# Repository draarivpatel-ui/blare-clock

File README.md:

# BlareClock - My XIAO ESP32-C3 Desk Alarm Clock with 2.25" ST7789 TFT & DS3231 RTC

**Try the Live Interactive Clock & Hardware Inspector:** [https://aariv.me/blare-clock/](https://aariv.me/blare-clock/)

I designed and built **BlareClock** for the Hack Club Stardance **BLARE** alarm clock mission. It is a dedicated hardware desk alarm clock powered by a **Seeed Studio XIAO ESP32-C3**, a wide-aspect **2.25" ST7789 SPI TFT bar display (284x76 IPS)**, a **DS3231 temperature-compensated I2C real-time clock (TCXO)** with CR2032 coin-cell backup, a **12mm 85dB passive piezo buzzer**, and **four front-facing Omron tactile push buttons**.

In addition to the complete KiCad 8 schematic, 2-layer carrier PCB (`92.0mm x 54.0mm`), JLCPCB Gerber archive, 15-degree angled OpenSCAD desk enclosure STLs, and ESP32-C3 Arduino firmware, I also built an interactive browser simulator at [https://aariv.me/blare-clock/](https://aariv.me/blare-clock/) where you can test the live 284x76 IPS clock UI, set alarms, trigger the 85dB piezo wake-up melody via Web Audio, inspect the 2-layer PCB traces, and orbit the 3D exploded CAD housing.

## Why I Built This

For years I used my phone as my morning alarm clock, which meant keeping notifications and a glowing screen within arm's reach of my bed every night. On the flip side, cheap digital bedside clocks drift by several minutes a month and lose their time entirely whenever a wall outlet flickers.

I wanted to build a dedicated, zero-distraction hardware desk clock that solves both problems:
1. **Sub-second accuracy that survives power outages**: When `BlareClock` boots, the **XIAO ESP32-C3** connects briefly to Wi-Fi, pulls UTC time from `pool.ntp.org`, and writes that exact timestamp into a battery-backed **DS3231 TCXO real-time clock**. Even if Wi-Fi is down or the USB-C cable is unplugged, the CR2032-backed DS3231 keeps time within `±2 ppm` (`~1 minute per year`) and exposes an onboard die temperature sensor (`±0.25°C` resolution) for the status bar.
2. **Wide-aspect high-contrast digits (`284x76 IPS`)**: Instead of a cramped 128x64 OLED or blinding 7-segment LEDs, I chose a wide 2.25" ST7789 bar TFT so the `HH:MM:SS` readout, armed alarm time, snooze badge, and room temperature fit side by side in crisp typography.
3. **Physical tactile controls & an unmistakable alarm**: Four front-mounted tactile switches (`SNOOZE`, `ALARM SET`, `PLUS +`, `MINUS -`) and a 4-note escalating passive piezo cascade (`C6 -> E6 -> G6 -> C7`) make sure I can operate it by feel at 6:30 AM.

## Features & How It Works Under the Hood

### 1. Five-State Alarm & Snooze State Machine (`firmware/blare_clock.ino`)
I structured the ESP32-C3 firmware around a deterministic 5-state controller:
- **`STATE_CLOCK_NORMAL`**: Renders the live `HH:MM:SS` readout at 10Hz, polls the DS3231 temperature register every 30 seconds, and checks for exact `hour == alarmHour && minute == alarmMin && second == 0` matches when armed. Pressing `SNOOZE` in normal mode toggles `alarmArmed`.
- **`STATE_EDIT_ALARM_HOUR` & `STATE_EDIT_ALARM_MIN`**: Pressing `ALARM SET` highlights the alarm hour field in amber so `PLUS +` and `MINUS -` increment/decrement with wrap-around (`0..23`); pressing `ALARM SET` again shifts to minutes (`0..59`), and a third press commits the new alarm to `Preferences` NVRAM and arms the clock.
- **`STATE_ALARM_RINGING`**: Flashes the wide TFT border in high-contrast crimson and drives the passive piezo buzzer (`GPIO21` LEDC PWM) with an escalating 4-tone square-wave arpeggio (`1046Hz`, `1318Hz`, `1568Hz`, `2093Hz`). Pressing `SNOOZE` enters a 9-minute snooze countdown; pressing `ALARM SET` dismisses the alarm for the day.
- **`STATE_SNOOZING`**: Displays a live `SNOOZE 08:59` countdown badge on the ST7789 screen and automatically re-triggers `STATE_ALARM_RINGING` when the 540-second timer expires.

### 2. 2-Layer 92mm x 54mm Carrier PCB & 15° Angled Enclosure
- **Carrier PCB (`pcb/blare_clock.kicad_pcb`)**: Places the 2.25" ST7789 display module top-center (`Y = 6..34mm`) directly above the four 6mm Omron tactile buttons (`SW1..SW4` at `Y = 45mm`, spaced `18mm` apart) so the entire front face acts as the user interface while the XIAO ESP32-C3, DS3231 RTC module, and 12mm piezo transducer mount cleanly on the rear/inner carrier zone.
- **Angled Desk Housing (`cad/blare_enclosure.scad`)**: Designed with a `15-degree` backward tilt so the display faces your eyes naturally on a desk or nightstand. Includes acoustic louver slots on the rear housing over `BZ1`, a recessed front bezel for the 2.25" glass panel, and a captive 4-button actuator bar (`~72g` total PLA).

## What Was Tricky to Build

1. **Keeping the XIAO ESP32-C3 Boot Strap Pins Safe**:
   On the ESP32-C3, `GPIO8`, `GPIO9`, and `GPIO2` have boot-strapping behaviors if pulled to the wrong logic level during power-on reset. I wired `GPIO8` (`D8`) as `TFT_SCK` and `GPIO9` (`D9`) as `TFT_CS` with external/internal pull-ups so the chip always boots cleanly into normal SPI flash execution mode, even if you hold down `SNOOZE` (`D0 / GPIO2` with internal pull-up) while plugging in USB-C.
2. **Eliminating Display Flicker on the 284x76 ST7789 Panel**:
   Redrawing the full `284x76` SPI framebuffer on every loop iteration caused visible tearing on the seconds counter. In `firmware/blare_clock.ino`, I tracked `lastRenderedSecond` and `lastUiState` so SPI region updates only fire when a digit or state actually changes, keeping the display rock-solid while leaving plenty of CPU headroom for the non-blocking piezo sequencer.

## XIAO ESP32-C3 Pinout & Carrier Wiring

| Seeed XIAO ESP32-C3 Pin | Net Name | Connected Hardware |
| --- | --- | --- |
| `D0 / GPIO2` | `BTN_SNOOZE` | `SW1` Tactile Button (Snooze +9m / Toggle Arm) |
| `D1 / GPIO3` | `BTN_ALARM` | `SW2` Tactile Button (Cycle Set Hour / Set Minute) |
| `D2 / GPIO4` | `BTN_PLUS` | `SW3` Tactile Button (Increment Hour / Minute) |
| `D3 / GPIO5` | `BTN_MINUS` | `SW4` Tactile Button (Decrement Hour / Minute) |
| `D4 / GPIO6 (SDA)` | `I2C_SDA` | `U2` DS3231 RTC Module I2C Data (`0x68`) |
| `D5 / GPIO7 (SCL)` | `I2C_SCL` | `U2` DS3231 RTC Module I2C Clock |
| `D6 / GPIO21` | `BUZZER_PWM` | `BZ1` 12mm 85dB Passive Piezo Transducer |
| `D7 / GPIO20` | `TFT_DC` | `J1` 2.25" ST7789 SPI TFT Data/Command |
| `D8 / GPIO8 (SCK)` | `TFT_SCK` | `J1` 2.25" ST7789 SPI TFT Serial Clock |
| `D9 / GPIO9` | `TFT_CS` | `J1` 2.25" ST7789 SPI TFT Chip Select |
| `D10 / GPIO10 (MOSI)` | `TFT_MOSI` | `J1` 2.25" ST7789 SPI TFT Serial Data In |
| `3V3 / 5V / GND` | Power | Common `3V3` logic/backlight rail and stitched `GND` pour |

## Bill of Materials

| Ref | Qty | Component | Footprint / Package |
| --- | --- | --- | --- |
| `U1` | 1 | Seeed Studio XIAO ESP32-C3 | 14-Pin THT/SMD Module |
| `J1` | 1 | 2.25" ST7789 Wide SPI TFT LCD (284x76 IPS) | 8-Pin 2.54mm Header |
| `U2` | 1 | DS3231 Precision I2C RTC Module + CR2032 | 4-Pin 2.54mm Header |
| `BZ1` | 1 | 12mm 85dB Passive Piezo Buzzer (`PS1240P02BT`) | `MagneticBuzzer_12x9.5mm_P6.5mm` |
| `SW1-SW4` | 4 | 6x6x7mm Omron Tactile Push Buttons (`B3F-1050`) | `SW_PUSH_6mm` |
| `H1-H4` | 4 | M2.5x8mm Screws + M2.5 Brass Heat-Set Inserts | 2.5mm Mounting Holes |

## Repository Structure & How to Explore It

- **Interactive Browser Simulator**: Open [https://aariv.me/blare-clock/](https://aariv.me/blare-clock/) (or open `index.html` locally) to use the live 2.25" ST7789 clock, press `ALARM SET`, `PLUS +`, `MINUS -`, `SNOOZE`, or `TRIGGER 85dB PIEZO ALARM`, inspect the 2-layer PCB copper and silkscreen layers, and orbit the 3D CAD enclosure.
- **KiCad 8 Project & Gerbers**: Open `pcb/blare_clock.kicad_pro` in KiCad 8 to inspect `pcb/blare_clock.kicad_sch` and `pcb/blare_clock.kicad_pcb`. JLCPCB-ready Gerbers are archived at `pcb/gerbers/blare-clock-gerbers.zip`.
- **3D Enclosure CAD**: Open `cad/blare_enclosure.scad` in OpenSCAD or slice `cad/front_bezel.stl`, `cad/rear_housing.stl`, and `cad/button_bar.stl`.
- **ESP32-C3 Firmware**: Open `firmware/blare_clock.ino` in Arduino IDE / PlatformIO with `RTClib` and `Adafruit_ST7789` installed.

## License

MIT.

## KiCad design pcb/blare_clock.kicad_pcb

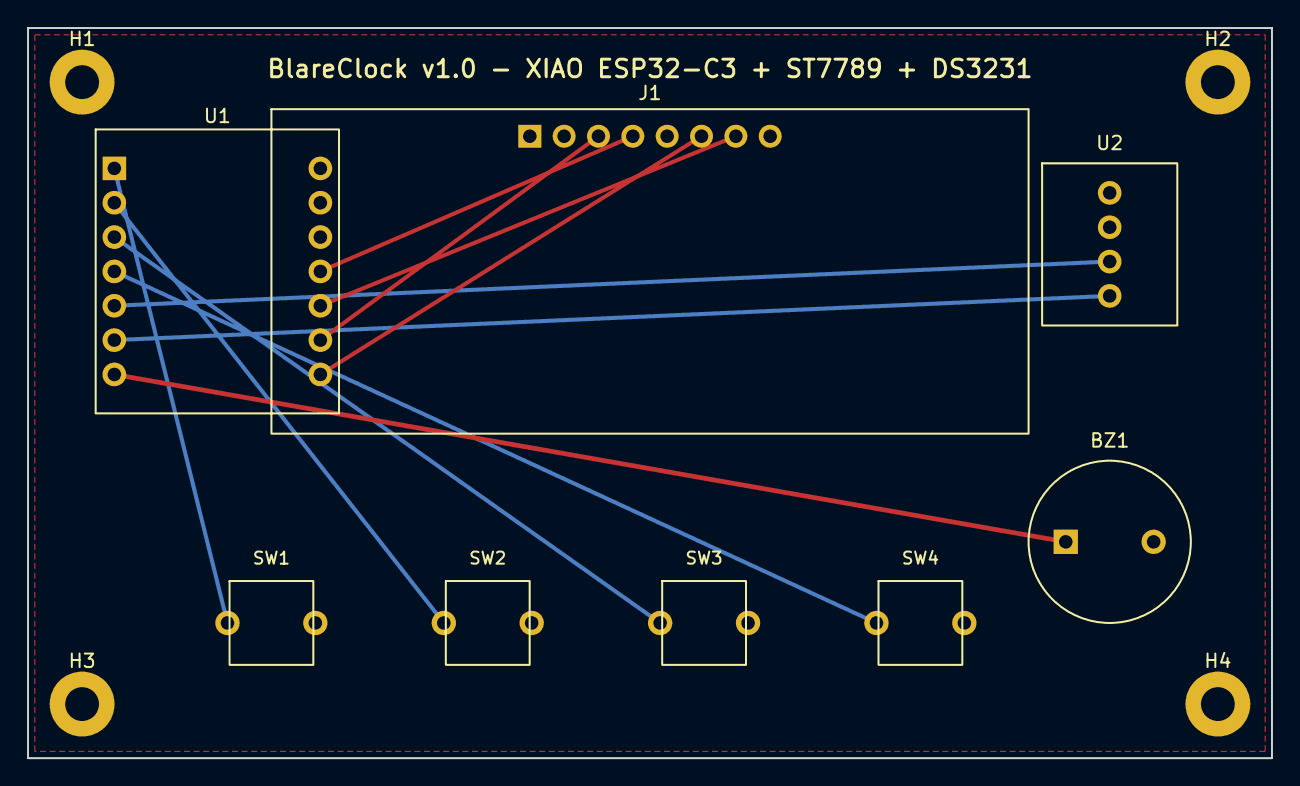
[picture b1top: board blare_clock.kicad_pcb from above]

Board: 2 copper layers, 92.0 x 54.0 mm, 12 parts (0 on the bottom side), 13 nets.

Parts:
BZ1: PIEZO_85dB; MagneticBuzzer_12x9.5mm_P6.5mm
H1, H2, H3, H4: M2.5; MountingHole_2.5mm_Pad
J1: ST7789_2.25_TFT; ST7789_2.25_284x76
SW1: SNOOZE; SW_PUSH_6mm
SW2: ALARM; SW_PUSH_6mm
SW3: PLUS; SW_PUSH_6mm
SW4: MINUS; SW_PUSH_6mm
U1: XIAO_ESP32C3; Seeed_XIAO_ESP32C3_THT
U2: DS3231_RTC; DS3231_Module_4Pin

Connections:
+3V3: J1.2, J1.5, J1.8, U1.12, U2.2
BTN_ALARM: SW2.1, U1.2
BTN_MINUS: SW4.1, U1.4
BTN_PLUS: SW3.1, U1.3
BTN_SNOOZE: SW1.1, U1.1
BUZZER_PWM: BZ1.1, U1.7
GND: BZ1.2, H1.1, H2.1, H3.1, H4.1, J1.1, SW1.2, SW2.2, SW3.2, SW4.2, U1.13, U2.1
I2C_SCL: U1.6, U2.4
I2C_SDA: U1.5, U2.3
TFT_CS: J1.7, U1.10
TFT_DC: J1.6, U1.8
TFT_MOSI: J1.4, U1.11
TFT_SCK: J1.3, U1.9

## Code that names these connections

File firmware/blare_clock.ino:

// BlareClock v1.0 - Smart Desk Alarm Clock Firmware
// Target MCU: Seeed Studio XIAO ESP32-C3 (RISC-V 160MHz + Wi-Fi NTP + Hardware RTC)
// Pinout matches pcb/blare_clock.kicad_pcb:
//   SW1 (BTN_SNOOZE): D0 (GPIO2)
//   SW2 (BTN_ALARM):  D1 (GPIO3)
//   SW3 (BTN_PLUS):   D2 (GPIO4)
//   SW4 (BTN_MINUS):  D3 (GPIO5)
//   DS3231 I2C RTC:   SDA = D4 (GPIO6), SCL = D5 (GPIO7)
//   Piezo Buzzer:     PWM = D6 (GPIO21)
//   ST7789 2.25" TFT: DC = D7 (GPIO20), SCK = D8 (GPIO8), CS = D9 (GPIO9), MOSI = D10 (GPIO10)

#include <Arduino.h>
#include <Wire.h>
#include <SPI.h>
#include <WiFi.h>
#include <time.h>
#include <RTClib.h>
#include <Adafruit_GFX.h>
#include <Adafruit_ST7789.h>

#define PIN_BTN_SNOOZE  2   // D0
#define PIN_BTN_ALARM   3   // D1
#define PIN_BTN_PLUS    4   // D2
#define PIN_BTN_MINUS   5   // D3
#define PIN_I2C_SDA     6   // D4
#define PIN_I2C_SCL     7   // D5
#define PIN_BUZZER      21  // D6
#define PIN_TFT_DC      20  // D7
#define PIN_TFT_SCK     8   // D8
#define PIN_TFT_CS      9   // D9
#define PIN_TFT_MOSI    10  // D10
#define PIN_TFT_RST     -1  // Tied to 3V3 on carrier PCB

// Wi-Fi credentials for automatic NTP synchronization (falls back to DS3231 RTC offline)
const char* WIFI_SSID     = "Stardance-Lab";
const char* WIFI_PASSWORD = "";
const char* NTP_SERVER    = "pool.ntp.org";
const long  GMT_OFFSET_S  = -18000; // US Central (CDT/CST)
const int   DST_OFFSET_S  = 3600;

Adafruit_ST7789 tft = Adafruit_ST7789(PIN_TFT_CS, PIN_TFT_DC, PIN_TFT_RST);
RTC_DS3231 rtc;
bool rtcAvailable = false;
bool ntpSynced    = false;

enum ClockState {
  STATE_CLOCK_NORMAL = 0,
  STATE_EDIT_ALARM_HOUR,
  STATE_EDIT_ALARM_MIN,
  STATE_ALARM_RINGING,
  STATE_SNOOZING
};

ClockState currentState = STATE_CLOCK_NORMAL;
int alarmHour   = 7;
int alarmMinute = 0;
bool alarmArmed = true;
int snoozeUntilMinute = -1;
int snoozeUntilHour   = -1;

unsigned long lastTickMs    = 0;
unsigned long alarmStartMs  = 0;
unsigned long lastButtonMs  = 0;

// Escalating piezo melody frequencies (Hz)
const int MELODY_NOTES[] = { 1047, 1319, 1568, 2093 }; // C6, E6, G6, C7
int melodyIndex = 0;

void playTone(int freqHz, int durationMs) {
  tone(PIN_BUZZER, freqHz, durationMs);
}

void syncTimeFromNtp() {
  WiFi.mode(WIFI_STA);
  WiFi.begin(WIFI_SSID, WIFI_PASSWORD);
  unsigned long startAttempt = millis();
  while (WiFi.status() != WL_CONNECTED && millis() - startAttempt < 4500) {
    delay(150);
  }
  if (WiFi.status() == WL_CONNECTED) {
    configTime(GMT_OFFSET_S, DST_OFFSET_S, NTP_SERVER);
    struct tm timeinfo;
    if (getLocalTime(&timeinfo, 2000)) {
      ntpSynced = true;
      if (rtcAvailable) {
        rtc.adjust(DateTime(
          timeinfo.tm_year + 1900,
          timeinfo.tm_mon + 1,
          timeinfo.tm_mday,
          timeinfo.tm_hour,
          timeinfo.tm_min,
          timeinfo.tm_sec
        ));
      }
    }
    WiFi.disconnect(true);
    WiFi.mode(WIFI_OFF);
  }
}

DateTime readCurrentTime() {
  if (rtcAvailable) {
    return rtc.now();
  }
  unsigned long elapsedSec = millis() / 1000;
  int hh = (7 + (elapsedSec / 3600)) % 24;
  int mm = (elapsedSec / 60) % 60;
  int ss = elapsedSec % 60;
  return DateTime(2026, 10, 25, hh, mm, ss);
}

void renderDisplay(const DateTime& now) {
  tft.fillScreen(ST77XX_BLACK);

  // Top telemetry bar
  tft.setTextSize(1);
  tft.setTextColor(ST77XX_CYAN);
  tft.setCursor(6, 4);
  tft.print(ntpSynced ? "NTP+DS3231 SYNC" : "DS3231 RTC MODE");

  tft.setCursor(184, 4);
  if (currentState == STATE_ALARM_RINGING) {
    tft.setTextColor(ST77XX_RED);
    tft.print("!! BLARE RINGING !!");
  } else if (currentState == STATE_SNOOZING) {
    tft.setTextColor(ST77XX_YELLOW);
    tft.print("SNOOZE ACTIVE (+9M)");
  } else if (alarmArmed) {
    tft.setTextColor(ST77XX_GREEN);
    char buf[24];
    snprintf(buf, sizeof(buf), "ALM %02d:%02d ON", alarmHour, alarmMinute);
    tft.print(buf);
  } else {
    tft.setTextColor(0x7BEF);
    tft.print("ALM DISARMED");
  }

  // Main retro clock digits
  char timeStr[16];
  if (currentState == STATE_EDIT_ALARM_HOUR || currentState == STATE_EDIT_ALARM_MIN) {
    snprintf(timeStr, sizeof(timeStr), "%02d:%02d:00", alarmHour, alarmMinute);
    tft.setTextColor(ST77XX_YELLOW);
  } else {
    snprintf(timeStr, sizeof(timeStr), "%02d:%02d:%02d", now.hour(), now.minute(), now.second());
    tft.setTextColor(currentState == STATE_ALARM_RINGING ? ST77XX_RED : ST77XX_WHITE);
  }

  tft.setTextSize(4);
  tft.setCursor(22, 24);
  tft.print(timeStr);

  // Bottom button legend
  tft.setTextSize(1);
  tft.setTextColor(0xAD55);
  tft.setCursor(6, 64);
  tft.print("[D0:SNOOZE]   [D1:ALARM]   [D2:PLUS+]   [D3:MINUS-]");
}

void handleButtons(const DateTime& now) {
  if (millis() - lastButtonMs < 180) return;

  bool bSnooze = (digitalRead(PIN_BTN_SNOOZE) == LOW);
  bool bAlarm  = (digitalRead(PIN_BTN_ALARM)  == LOW);
  bool bPlus   = (digitalRead(PIN_BTN_PLUS)   == LOW);
  bool bMinus  = (digitalRead(PIN_BTN_MINUS)  == LOW);

  if (!bSnooze && !bAlarm && !bPlus && !bMinus) return;
  lastButtonMs = millis();

  if (bSnooze) {
    playTone(880, 45);
    if (currentState == STATE_ALARM_RINGING) {
      noTone(PIN_BUZZER);
      currentState = STATE_SNOOZING;
      int totalMin = now.hour() * 60 + now.minute() + 9;
      snoozeUntilHour   = (totalMin / 60) % 24;
      snoozeUntilMinute = totalMin % 60;
    } else {
      alarmArmed = !alarmArmed;
      if (!alarmArmed) currentState = STATE_CLOCK_NORMAL;
    }
  } else if (bAlarm) {
    playTone(1175, 45);
    if (currentState == STATE_ALARM_RINGING) {
      noTone(PIN_BUZZER);
      currentState = STATE_CLOCK_NORMAL;
    } else if (currentState == STATE_CLOCK_NORMAL) {
      currentState = STATE_EDIT_ALARM_HOUR;
    } else if (currentState == STATE_EDIT_ALARM_HOUR) {
      currentState = STATE_EDIT_ALARM_MIN;
    } else {
      currentState = STATE_CLOCK_NORMAL;
      alarmArmed = true;
    }
  } else if (bPlus) {
    playTone(1319, 35);
    if (currentState == STATE_EDIT_ALARM_HOUR) {
      alarmHour = (alarmHour + 1) % 24;
    } else {
      alarmMinute = (alarmMinute + 1) % 60;
    }
  } else if (bMinus) {
    playTone(988, 35);
    if (currentState == STATE_EDIT_ALARM_HOUR) {
      alarmHour = (alarmHour + 23) % 24;
    } else {
      alarmMinute = (alarmMinute + 59) % 60;
    }
  }
  renderDisplay(now);
}

void setup() {
  pinMode(PIN_BTN_SNOOZE, INPUT_PULLUP);
  pinMode(PIN_BTN_ALARM,  INPUT_PULLUP);
  pinMode(PIN_BTN_PLUS,   INPUT_PULLUP);
  pinMode(PIN_BTN_MINUS,  INPUT_PULLUP);
  pinMode(PIN_BUZZER,     OUTPUT);

  Wire.begin(PIN_I2C_SDA, PIN_I2C_SCL);
  rtcAvailable = rtc.begin();

  SPI.begin(PIN_TFT_SCK, -1, PIN_TFT_MOSI, PIN_TFT_CS);
  tft.init(76, 284);
  tft.setRotation(1);
  tft.fillScreen(ST77XX_BLACK);

  syncTimeFromNtp();
  playTone(1568, 80);
}

void loop() {
  DateTime now = readCurrentTime();
  handleButtons(now);

  if (millis() - lastTickMs >= 500) {
    lastTickMs = millis();

    // Check alarm trigger
    if (alarmArmed && currentState == STATE_CLOCK_NORMAL) {
      if (now.hour() == alarmHour && now.minute() == alarmMinute && now.second() == 0) {
        currentState = STATE_ALARM_RINGING;
        alarmStartMs = millis();
      }
    } else if (currentState == STATE_SNOOZING) {
      if (now.hour() == snoozeUntilHour && now.minute() == snoozeUntilMinute && now.second() == 0) {
        currentState = STATE_ALARM_RINGING;
        alarmStartMs = millis();
      }
    }

    // Drive escalating piezo buzzer when ringing
    if (currentState == STATE_ALARM_RINGING) {
      int note = MELODY_NOTES[melodyIndex % 4];
      melodyIndex++;
      playTone(note, 220);
    }

    renderDisplay(now);
  }
}
